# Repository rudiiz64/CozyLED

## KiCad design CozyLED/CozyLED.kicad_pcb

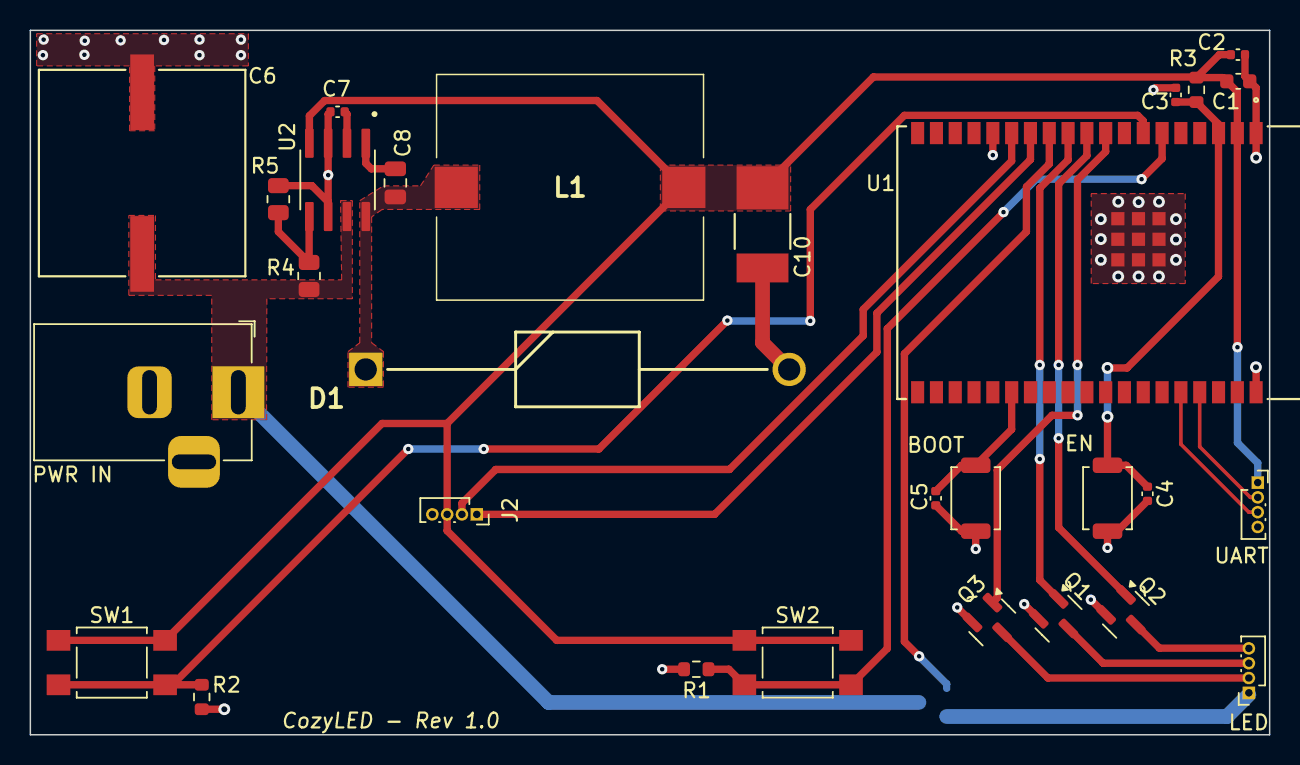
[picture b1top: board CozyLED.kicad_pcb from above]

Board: 2 copper layers, 83.7 x 47.6 mm, 30 parts (1 on the bottom side), 23 nets.

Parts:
BOOT: BOOT; SW_SPST_TS-1088-xR020
C1: 22u; C_0603_1608Metric
C2, C3, C4, C7: 0.1u; C_0402_1005Metric
C5: 0.1u (NC); C_0402_1005Metric
C6: 47u; CAP_EEFK_H13_PAN
C8: 0.1u, 0805; C_0805_2012Metric
C10: 47u; PCAP_594D_C_VIS
D1: SB5H100; DIOAD2855W132L835D505
EN: EN; SW_SPST_TS-1088-xR020
J2: LCD DISPLAY; PinSocket_1x04_P1.00mm_Vertical
L1: DO5022P-154MLD; DO5022P154MLD
LED: LED Pins; PinSocket_1x04_P1.00mm_Vertical
PWR IN: Barrel_Jack_Switch; BarrelJack_Horizontal
Q1, Q2, Q3, Q4: AO3400A; SOT-23
R1, R2: 100k; R_0603_1608Metric
R3: 10k; R_0603_1608Metric
R4: 1M, 0805; R_0805_2012Metric
R5: 384k, 0805; R_0805_2012Metric
SW1: LEFT; SW_SPST_TL3305A
SW2: RIGHT; SW_SPST_TL3305A
U1: ESP32-WROVER-E-N16R8; ESP32-WROVER-E_EXP
U2: MAX5033AASA_T; SOIC127P600X175-8N
UART: UART; PinSocket_1x04_P1.00mm_Vertical

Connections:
+3V3: C1.2, C2.2, C10.1, J2.3, L1.2, R3.1, SW1.1, SW2.1, U1.2 (3V3), U2.4 (FB), UART.1
+12V: C6.2, PWR IN.1, Q4.3 (D), R4.1, U2.7 (VIN)
/BOOT: BOOT.2, C5.1, U1.25 (IO0)
/BST: C8.2, U2.1 (BST)
/EN: C3.2, C4.1, EN.2, R3.2, U1.3 (EN)
/GPIO_B: Q3.1 (G), U1.9 (IO33)
/GPIO_G: Q2.1 (G), U1.10 (IO25)
/GPIO_PWR: Q4.1 (G), U1.12 (IO27)
/GPIO_R: Q1.1 (G), U1.11 (IO26)
/LBTN: R2.1, SW1.2, U1.7 (IO35)
/LED_B: LED.2, Q3.3 (D)
/LED_G: LED.4, Q2.3 (D)
/LED_PWR: LED.1, Q4.2 (S)
/LED_R: LED.3, Q1.3 (D)
/RBTN: R1.1, SW2.2, U1.6 (IO34)
/RXD0: U1.34 (RXD0), UART.3
/SCL: J2.2, U1.14 (IO12)
/SDA: J2.1, U1.13 (IO14)
/TXD0: U1.35 (TXD0), UART.2
GND: BOOT.1, C1.1, C2.1, C3.1, C4.2, C5.2, C6.1, C7.1, C10.2, D1.2 (A), EN.1, J2.4, PWR IN.2, PWR IN.3, Q1.2 (S), Q2.2 (S), Q3.2 (S), R1.2, R2.2, R5.2, U1.1 (GND), U1.15 (GND), U1.38 (GND), U1.39 (EPAD), U1.40 (EPAD), U1.41 (EPAD), U1.42 (EPAD), U1.43 (EPAD), U1.44 (EPAD), U1.45 (EPAD), U1.46 (EPAD), U1.47 (EPAD), U2.3 (SGND), U2.6 (GND), UART.4
unnamed: C8.1, D1.1 (K), L1.1, U2.8 (LX)
unnamed: R4.2, R5.1, U2.5 (ON/~OFF)
unnamed: C7.2, U2.2 (VD)

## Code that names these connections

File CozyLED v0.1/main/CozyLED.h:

#ifndef COZYLED_H
#define COZYLED_H

#include <inttypes.h>

// Variable Defines
#define HOLD_TIMER      250
#define INIT_CHECK      9

// I2C Defines
#define I2C_ADDR        0x3C
#define I2C_SLAVE_NUM   I2C_NUM_0

// LCD Defines
#define DISPL_X         0x80
#define DISPL_Y         0x40
#define LEFT_TRI_X      0x05

#define RIGHT_TRI_X     0x7B        // 112 x
#define TRI_Y           0x20        // 32 y
#define TRI_0           0xFF
#define TRI_1           0x7E
#define TRI_2           0x3C
#define TRI_3           0x18

// GPIO Defines
#define LED_R           GPIO_NUM_26
#define LED_G           GPIO_NUM_25
#define LED_B           GPIO_NUM_33
#define LED_PWR         GPIO_NUM_27
#define L_BTN           GPIO_NUM_35
#define R_BTN           GPIO_NUM_34
#define SDA             GPIO_NUM_14
#define SCL             GPIO_NUM_12

// LED Bit Mask
#define LED_R_BIT_MASK (1ULL << LED_R)
#define LED_G_BIT_MASK (1ULL << LED_G)
#define LED_B_BIT_MASK (1ULL << LED_B)

// LED Controller Defines
#define LEDC_MODE       LEDC_LOW_SPEED_MODE
#define LEDC_DUTY_RES   LEDC_TIMER_13_BIT   // Set duty resolution to 13-bits

#define LEDC_DUTY          (2048)              // Set duty to 25% (2 ** 13) * 25% = 2048
#define LEDC_MAX_FREQUENCY (5000)              // Frequency in Hz
#define LEDC_FREQUENCY     (2500)
#define LEDC_FREQ_CHANGE   (500)               // Incremental change to frequency value
#define LEDC_MAX_RES       (8192)             // Max duty 90% (2 ** 13) * 90% ~ 7373
#define LEDC_ON            (819)              // output inverted, using 10% as 90%

enum STATE {
    INIT = 0,
    RGB,
    YTP,
    BREATHE,
    WAVE
};

enum NEXT_COLOR {
    RED = 0,
    YELLOW,
    GREEN,
    TEAL,
    BLUE,
    PURPLE
};

enum PIN {
    NONE = 0,
    LEFT,
    RIGHT
};

struct btn_status {
    const uint8_t PIN;
    volatile bool pressed;
    volatile bool locked;
};



#endif

/*// Breathing Function
        
        for (;;){
            // LED 100% Duty
            //printf("LEDC Set duty = %d\n\n", LED_Duty);
            if (LED_Duty - dutyChange < 0){                     // If next duty change is zero or negative, enter
                LED_Duty -= LED_Duty;                           // Instead of entering negative, we hit zero
                dutyChange *= -1;
            }
            else if (LED_Duty - dutyChange > LEDC_MAX_RES){     // If we are going to exceed the max resolution value, enter
                LED_Duty += (LEDC_MAX_RES - LED_Duty);          // We add the remainder of LED_Duty to hit max res 
                dutyChange *= -1;
            }
            ledc_set_duty(LEDC_MODE, LEDC_CHANNEL, LED_Duty);
            ledc_update_duty(LEDC_MODE, LEDC_CHANNEL);
            printf("Duty: %ld\n",ledc_get_duty(LEDC_MODE, LEDC_CHANNEL));

            vTaskDelay(100 / portTICK_PERIOD_MS);
            LED_Duty -= dutyChange;
        }*/

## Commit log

2023-10-02 Rev 0.1
    + Created project
    + Created symbol for ESP32 MINI 2
2023-10-19 Updated CozyLED
    + Adjusted footprint of ESP32 to account for ground pins at center
    + Adjusted ESP32 MINI 2 footprint to account only for peripheral GPIO
    + Updated MOSFETs to control grounding of LED strips
    + Updated LED strip to be based off 12V instead of 5V
    + Laid out board and component placement on 2 layers
2026-02-18 Updated v0.1
    - Added documentation
    - Designed initial state machine
    - Tested state machine to correctly initialize then enter default
    - Added initial LED code for static color
    - Added initial LED code for breathing color
2026-02-19 Updated code
    - Implemented initial interrupts for button with some debounce
    - Debounce needs improvement
    - Need to debug ISR call (one press calls both?)
    - Need to debug why ISR is called when finger is close to pressing button but not physically pressing it (emf?)
2026-02-20 Updated Rev 0.1 code
    Update
    - Squashed some bugs regarding button presses
    - Added button press to LED
    - Debounce needs some work, but buttons not correctly shift through R -> G -> B and vice versa, depending on what button is pressed
    Issues
    - RGB works inversely (false turns on, true turns off) need to debug this
2026-02-23 Updated code
    Updates:
    - Designed color transition map
    - Added previous button press check to determine whether to disable previous or current color for RGB states
    - Tested and verified color transition map with new check, color now correctly transitions despite which direction
    To do:
    - Implement transition to utilize breathing mode (button hold)
2026-03-02 Updated Code v0.1
    Updates
    - Added code for LCD drawings of mode label and triangles to depict button presses (still need actual press drawing)
    - Added initial code for mode transition by button hold (2.5 seconds for now)
    - Cleaned up some test code
2026-03-05 Updated code v0.1
    Updates:
    - Implemented mode transition via polling a button hold
    - Added safeguards to prevent static debounce from initial press
    - Added button "lockout" for a press or hold to prevent improper state transition and submode selection
    - Tested and validated proper mode transition via FSM from button hold (short and long hold), proper RGB submode in static transition
2026-03-09 Update CozyLED.c
    Updates:
    - Updated documentation for the LED FSM
    - Added initial implementation of the ESP32 LED controller for each color line
    - Cleaned up some code
    - Added duty var to the LED struct
2026-03-09 Updated CozyLED schematic
    Updates
    - Placed initial components of board in schematic
    - Redesigning schematic to not be devboard based but solely ESP32 WROVER-E
    - Need to add all the ESP32 components and the DC-DC converter (12V -> 3V3)
2026-03-10 Updated CozyLED PCB
    Updates
    - Added 12V to 3.3V sw reg (sym+footprint) with its circuitry
    - Changed ESP32 symbol to S3 WROVER-E (was incorrectly S2 WROOM) with required circuitry
    - Added EN&BOOT buttons
    - Added breakout pins for UART, LED, and LCD
    - Added nMOS transistors for RGB control (need to change source)
2026-03-11 Updated CozyLED schematic
    Updates
    - Added footprints for each component
    - Added symbols, footprints, and 3D models for the DC-DC converter's components
2026-03-13 Updated CozyLED PCB
    Updates:
    - Finalized initial revision of schematic (footprints)
    - Initial placement of components in layout
    - Initial board margins
2026-03-19 Updated CozyLED schematic and PCB
    Updates
    - Changed version from Rev B to Rev 1.0
    - Revised board to be longer and thinner, since it looked ugly as heck
    - Added a missing transistor for the power control on the LED output because I'm dumb as shit and forgot to add one
    - Added some nice text to the silkscreen so people know what the name is
2026-03-31 Updated CozyLED code 0.1
    Updates
    - Transitioning gpio calls for the LED ouputs to be ESP32 LED controller channels for duty cycle control
    - Added LED startup pattern for pizzaz
    - Cleaned up some code
    Issues
    - Start up colors are not correct
2026-04-01 Updated CozyLED rev 0.1 code
    Updates
    - Fixed the button issue!!! The clear on button press was not being correctly activated so it the program was perma stuck in whatever button was pressed first.
    - Finalized initial setting of LED control module in code, testing required to verify correctness
    Issues
    - Starting color is incorrect and the behavior is odd. Outside initialization, updating the duty of each control line works correctly, but in the initialization, the duty setting is inverted. Startin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
    - Due to incorrect color, the transition is incorrect.
2026-04-02 Updated CozyLED v0.1 code!!
    Updates:
    - Fixed the color issue! (Brief rundown of what was happening: outputs were acting inverted due to an internal var in the struct for the LED controller that was setting the output to be inverted. I t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
    - Cleaned up some old code, needs more spring cleaning!
    Issues:
    - On initial startup of entering the static state, the button fails to work. After one press, the system becomes responsive. There is probably an initial check I left that is discarding the initial pr
2026-04-03 Updated CozyLED rev 0.2
    Updates
    - Absolute headache.
    - Initial implementation of the wave function
    - Added a var to determine what is happening (2 ON, 1 ON) for color transition
    - Added initial frequency value and its delta
    - 6 7!!!!!!
2026-04-06 Updated CozyLED rev 0.2 code
    Updates:
    - Color now transitions!!! Color will transition from starting color and change in a fashion of R -> Y -> G -> T -> B -> P -> R
    - Added safety nets to prevent overflow and underflow of the bounds
    - Cleaned up some code
    Issues
    - Changing modes with information from static that transitioned from a left button press will result in the wave state bugging out since the channels are reversed. Need to account for reversed channe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
2026-04-08 Updated CozyLED rev 0.2
    Updates
    - Wave now accounts for previous button presses (if user holds LEFT to mode change from static, color shifts in a reverse pattern, if user holds RIGHT to mode change from BREATHE, color shifts normal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
    - Added a "default" when transitioning modes from WAVE, now will automatically soft reset the color to what it was in regardless of current duty cycle
    - Fixed the button lock out
    Issues
    - Transitioning from WAVE to STATIC in certain colors will result in a soft or hard reset
